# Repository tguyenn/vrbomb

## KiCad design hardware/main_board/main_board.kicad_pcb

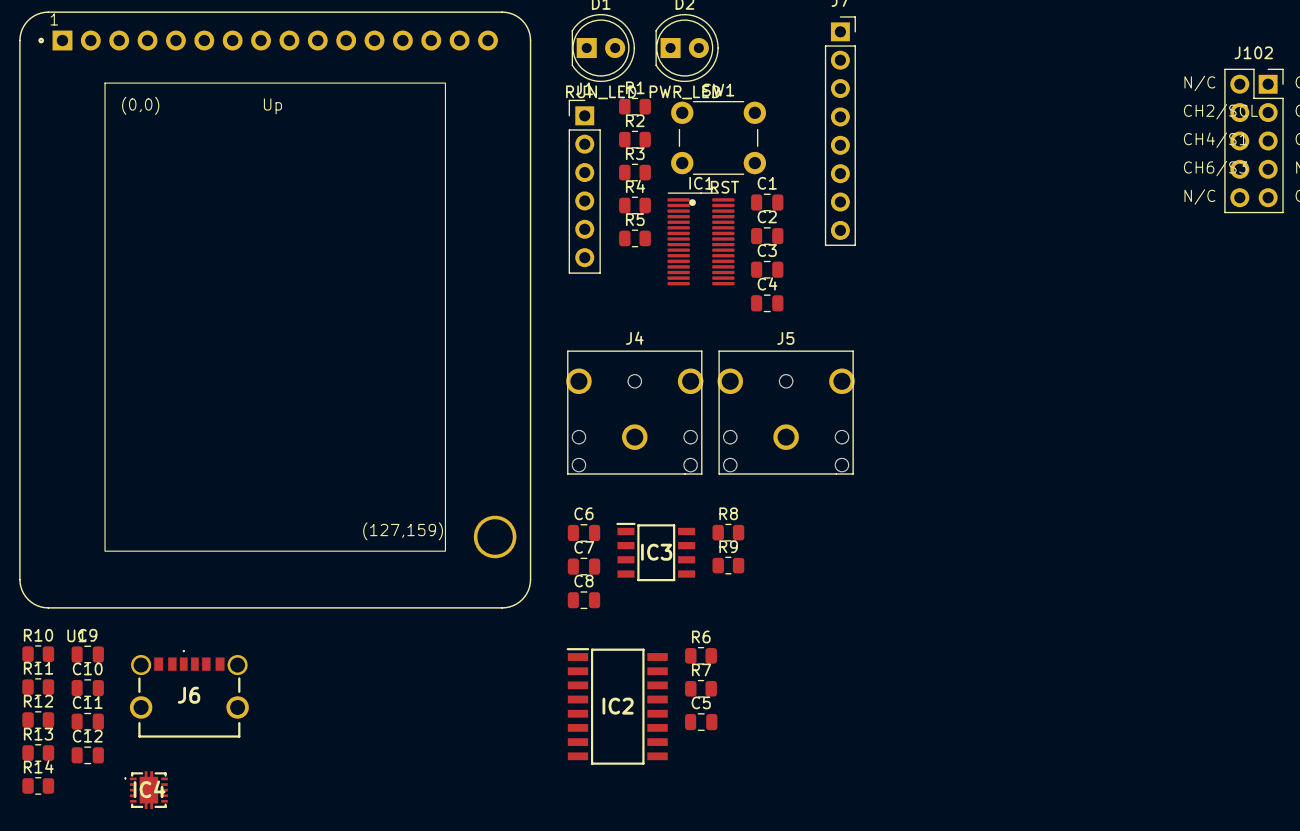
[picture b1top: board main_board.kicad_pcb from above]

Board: 2 copper layers, 40 parts (0 on the bottom side), 41 nets, no tracks yet.

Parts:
C1: 0.47uF; C_0805_2012Metric
C2: 10nF; C_0805_2012Metric
C3: 10uF; C_0805_2012Metric
C4: 0.1uF; C_0805_2012Metric
C5, C6, C8: 1u; C_0805_2012Metric
C7: 0u33; C_0805_2012Metric
C9, C10, C11: 10u; C_0805_2012Metric
C12: u1; C_0805_2012Metric
D1: RUN_LED; LED_D5.0mm
D2: PWR_LED; LED_D5.0mm
IC1: M0G3507QDGS32RQ1; generic_VSSOP_0.5mm
IC2: SN74HC157NSR; SOIC127P780X200-16N
IC3: LM4890M_NOPB; ti_LM4890M_NOPB
IC4: TPS63000IDRCRQ1
J1: Conn_01x06_Pin; PinHeader_1x06_P2.54mm_Vertical
J4, J5: AudioJack; Jack_3.5mm_CUI_SJ1-3523N_Horizontal
J6: UJC-H-G-SMT-1-P6-TR; UJCHGSMT1P6TR
J7: 1x8 Male Pins; PinSocket_1x08_P2.54mm_Vertical
J102: 2x5 Socket Pins; PinSocket_2x05_P2.54mm_Vertical
R1, R2, R6, R7: 10k; R_0805_2012Metric
R3: 47k; R_0805_2012Metric
R4, R5: 470; R_0805_2012Metric
R8, R9: 20k; R_0805_2012Metric
R10: 100; R_0805_2012Metric
R11: 1M; R_0805_2012Metric
R12, R13: 5k1; R_0805_2012Metric
R14: 200k; R_0805_2012Metric
SW1: RST; SW_PUSH_6mm
U1: HiLetGo_ST7735R; hiletgo_st7735r

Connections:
+3V3: C3.1, C4.1, C10.1, C11.1, IC1.7 (VDD), IC4.1 (VOUT), J1.5, R1.2, R2.2, R3.1, R5.1, R6.2, R7.2, R11.1, U1.2 (VCC), U1.6 (RESET), U1.15 (LED+)
+5V: C6.2, C9.1, IC3.6 (VDD), IC4.5 (VIN), J6.A9 (VBUS), J6.B9 (VBUS), J7.1, R10.1
/Audio IO/ADC_IN: IC1.21 (PA14/CLK_OUT/A0_12), J5.R (ring), J5.T (tip)
/Audio IO/DAC_OUT: C7.1, IC1.22 (PA15/A1_0/DACOUT)
/Encoders & Buttons/ENC1.SW: IC2.2 (1A), R6.1
/Encoders & Buttons/ENC2.SW: IC2.3 (1B), R7.1
/Encoders & Buttons/ENC.CLK: IC1.1 (PA26/A0_1), IC2.9 (3Y)
/Encoders & Buttons/ENC.DT: IC1.2 (PA27/RTC_OUT/A0_0), IC2.7 (2Y)
/Encoders & Buttons/ENC.SW: IC1.28 (PA21/A1_7/VREF-), IC2.4 (1Y)
/Encoders & Buttons/ENC_TOGGLE: IC1.32 (PA25/A0_2), IC2.1 (~A/B)
/LCD/CS_LCD: IC1.10 (PA3/LFXIN), U1.10 (TFT_CS)
/LCD/CS_SD: IC1.9 (PA2/ROSC), U1.14 (SDC_CS)
/LCD/LCD_DC: IC1.14 (PA7/CLK_OUT), U1.7 (TFTDC)
/LCD/SPI0.MISO: IC1.11 (PA4/LFCLK_IN/LFXOUT), U1.12 (SDC_MISO)
/LCD/SPI0.MOSI: IC1.12 (PA5/HFXIN/FCC_IN), U1.8 (TFTMOSI), U1.13 (SDC_MOSI)
/LCD/SPI0.SCK: IC1.13 (PA6/HFCLK_IN/HFXOUT), U1.9 (TFTSCK), U1.11 (SDCSCK)
/MCU/BSL_INVOKE: IC1.25 (PA18/A1_3), J1.1
/MCU/I2C0.SCL: IC1.5 (PA1), R1.1
/MCU/I2C0.SDA: IC1.4 (PA0), R2.1
/MCU/NRST: C2.1, IC1.6 (NRST), J1.4, R3.2, SW1.2
/MCU/RUN_LED: IC1.15 (PA8), R4.1
/MCU/S0: IC1.17 (PA10/CLK_OUT), J7.4
/MCU/S1: IC1.18 (PA11), J7.5
/MCU/S2: IC1.19 (PA12/FCC_IN), J7.6
/MCU/S3: IC1.20 (PA13), J7.7
/MCU/SWCLK: IC1.27 (PA20/SWCLK), J1.2
/MCU/SWDIO: IC1.26 (PA19/SWDIO), J1.3
GND: C1.2, C2.2, C3.2, C4.2, C5.2, C6.1, C8.2, C12.2, D1.1 (K), D2.1 (K), IC1.8 (VSS), IC2.8 (GND), IC2.15 (~G), IC3.1 (~SHUTDOWN), IC3.7 (GND), IC4.9 (GND), J1.6, J4.S (sleeve), J5.S (sleeve), J6.A12 (GND), J6.B12 (GND), J7.8, J102.9, R12.2, R13.2, R14.2, SW1.1, U1.1 (GND), U1.16 (LED-)
GNDPWR: C9.2, C10.2, C11.2, IC4.3 (PGND_1), IC4.11 (PGND_2), IC4.12 (PGND_3), IC4.13 (PGND_4), IC4.14 (PGND_5), IC4.15 (PGND_6)
unnamed: C7.2, R8.1
unnamed: D1.2 (A), R4.2
unnamed: D2.2 (A), R5.2
unnamed: C1.1, IC1.3 (VCORE)
unnamed: C5.1, IC2.16 (VCC)
unnamed: C8.1, IC3.2 (BYPASS), IC3.3 (+IN)
unnamed: IC3.4 (-IN), R8.2, R9.1
unnamed: IC3.5 (VO_1), J4.R (ring), J4.T (tip), R9.2
unnamed: C12.1, IC4.6 (EN), IC4.7 (PS/SYNC), IC4.8 (VINA), R10.2
unnamed: IC4.10 (FB), R11.2, R14.1
unnamed: J6.A5 (CC1), R13.1
unnamed: J6.B5 (CC2), R12.1

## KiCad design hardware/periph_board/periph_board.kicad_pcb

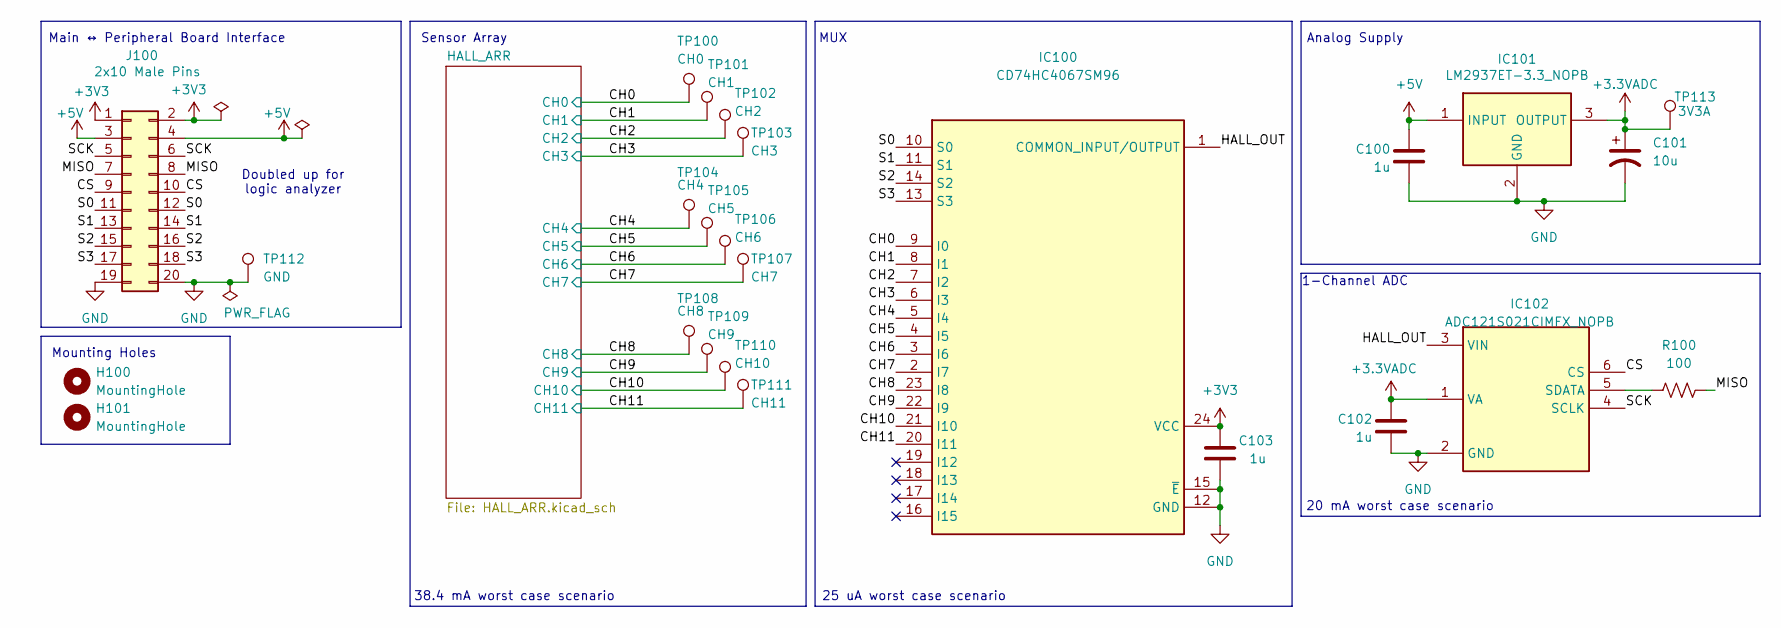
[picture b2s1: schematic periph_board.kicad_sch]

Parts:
C100, C102, C103: 1u; C_0805_2012Metric_Pad1.18x1.45mm_HandSolder
C101: 10u; C_0805_2012Metric
H100, H101: MountingHole; MountingHole_3.2mm_M3
IC100: CD74HC4067SM96; SOP65P780X200-24N; Mouser Part Number 595-CD74HC4067SM96
IC101: LM2937ET-3.3_NOPB; TO254P470X1028X1955-3P; Mouser Part Number 926-LM2937ET-3.3NOPB
IC102: ADC121S021CIMFX_NOPB; SOT95P280X145-6N; Mouser Part Number 926-A121S021CIMFXNPB
J100: 2x10 Male Pins; PinSocket_2x10_P2.54mm_Vertical
R100: 100; R_0805_2012Metric
TP100: CH0; bettertestpoint2
TP101: CH1; bettertestpoint2
TP102: CH2; bettertestpoint2
TP103: CH3; bettertestpoint2
TP104: CH4; bettertestpoint2
TP105: CH5; bettertestpoint2
TP106: CH6; bettertestpoint2
TP107: CH7; bettertestpoint2
TP108: CH8; bettertestpoint2
TP109: CH9; bettertestpoint2
TP110: CH10; bettertestpoint2
TP111: CH11; bettertestpoint2
TP112: GND; bettertestpoint2
TP113: 3V3A; bettertestpoint2

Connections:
+3.3VADC: C101.1, C102.2, IC101.3 (OUTPUT), IC102.1 (VA), TP113.1
+3V3: C103.2, IC100.24 (VCC), J100.1, J100.2; also elsewhere on the board
+5V: C100.2, IC101.1 (INPUT), J100.3, J100.4
/CH0: IC100.9 (I0), TP100.1; also elsewhere on the board
/CH1: IC100.8 (I1), TP101.1; also elsewhere on the board
/CH2: IC100.7 (I2), TP102.1; also elsewhere on the board
/CH3: IC100.6 (I3), TP103.1; also elsewhere on the board
/CH4: IC100.5 (I4), TP104.1; also elsewhere on the board
/CH5: IC100.4 (I5), TP105.1; also elsewhere on the board
/CH6: IC100.3 (I6), TP106.1; also elsewhere on the board
/CH7: IC100.2 (I7), TP107.1; also elsewhere on the board
/CH8: IC100.23 (I8), TP108.1; also elsewhere on the board
/CH9: IC100.22 (I9), TP109.1; also elsewhere on the board
/CH10: IC100.21 (I10), TP110.1; also elsewhere on the board
/CH11: IC100.20 (I11), TP111.1; also elsewhere on the board
/CS: IC102.6 (CS), J100.9, J100.10
/HALL_OUT: IC100.1 (COMMON_INPUT/OUTPUT), IC102.3 (VIN)
/MISO: J100.7, J100.8, R100.2
/S0: IC100.10 (S0), J100.11, J100.12
/S1: IC100.11 (S1), J100.13, J100.14
/S2: IC100.14 (S2), J100.15, J100.16
/S3: IC100.13 (S3), J100.17, J100.18
/SCK: IC102.4 (SCLK), J100.5, J100.6
GND: C100.1, C101.2, C102.1, C103.1, IC100.12 (GND), IC100.15 (~E), IC101.2 (GND), IC102.2 (GND), J100.19, J100.20, TP112.1; also elsewhere on the board
unnamed: IC102.5 (SDATA), R100.1

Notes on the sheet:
Mounting Holes
MUX
Analog Supply
Main ↔ Peripheral Board Interface
38.4 mA worst case scenario
1-Channel ADC
20 mA worst case scenario
Sensor Array
Doubled up for logic analyzer
25 uA worst case scenario

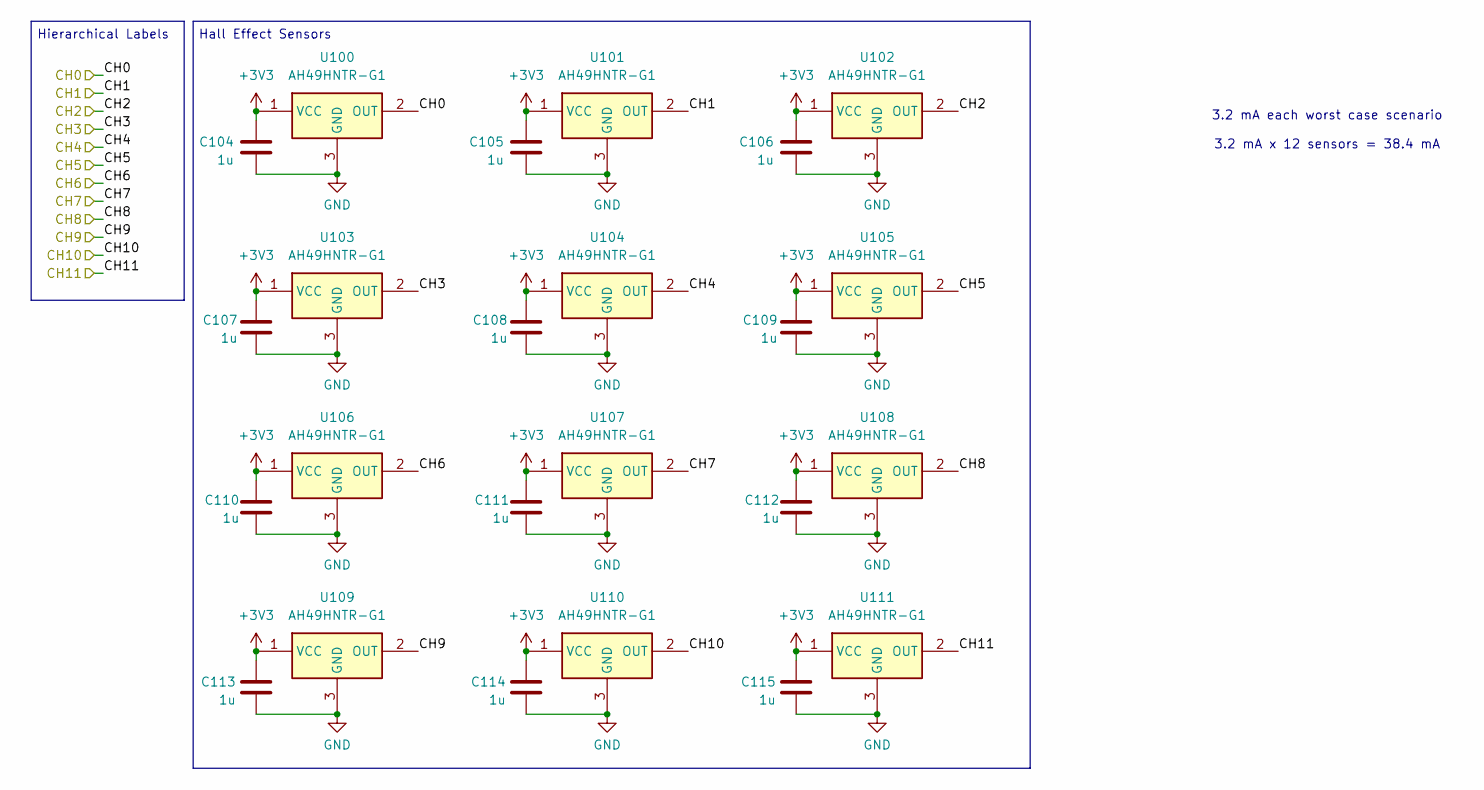
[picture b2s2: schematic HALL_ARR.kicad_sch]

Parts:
C104, C105, C106, C107, C108, C109, C110, C111, C112, C113, C114, C115: 1u; C_0805_2012Metric_Pad1.18x1.45mm_HandSolder
U100, U101, U102, U103, U104, U105, U106, U107, U108, U109, U110, U111: AH49HNTR-G1; SOT95P282X145-3N; Mouser Part Number 621-AH49HNTR-G1

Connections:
+3V3: C104.2, C105.2, C106.2, C107.2, C108.2, C109.2, C110.2, C111.2, C112.2, C113.2, C114.2, C115.2, U100.1 (VCC), U101.1 (VCC), U102.1 (VCC), U103.1 (VCC), U104.1 (VCC), U105.1 (VCC), U106.1 (VCC), U107.1 (VCC), U108.1 (VCC), U109.1 (VCC), U110.1 (VCC), U111.1 (VCC); also elsewhere on the board
/CH0: U100.2 (OUT); also elsewhere on the board
/CH1: U101.2 (OUT); also elsewhere on the board
/CH2: U102.2 (OUT); also elsewhere on the board
/CH3: U103.2 (OUT); also elsewhere on the board
/CH4: U104.2 (OUT); also elsewhere on the board
/CH5: U105.2 (OUT); also elsewhere on the board
/CH6: U106.2 (OUT); also elsewhere on the board
/CH7: U107.2 (OUT); also elsewhere on the board
/CH8: U108.2 (OUT); also elsewhere on the board
/CH9: U109.2 (OUT); also elsewhere on the board
/CH10: U110.2 (OUT); also elsewhere on the board
/CH11: U111.2 (OUT); also elsewhere on the board
GND: C104.1, C105.1, C106.1, C107.1, C108.1, C109.1, C110.1, C111.1, C112.1, C113.1, C114.1, C115.1, U100.3 (GND), U101.3 (GND), U102.3 (GND), U103.3 (GND), U104.3 (GND), U105.3 (GND), U106.3 (GND), U107.3 (GND), U108.3 (GND), U109.3 (GND), U110.3 (GND), U111.3 (GND); also elsewhere on the board

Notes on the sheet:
3.2 mA each worst case scenario 3.2 mA x 12 sensors = 38.4 mA
Hall Effect Sensors
Hierarchical Labels

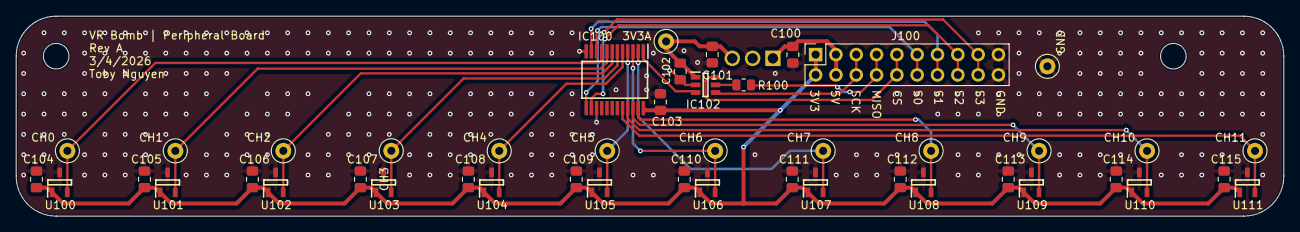
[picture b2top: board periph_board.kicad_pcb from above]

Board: 2 copper layers, 158.5 x 25.0 mm, 49 parts (1 on the bottom side), 25 nets.

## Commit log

2026-03-03 cleaned up unnecessary files
2026-03-03 add deadline
2026-03-05 scorched earth
2026-03-07 Adjusted spacing to 13.5mm between hall effects
2026-03-08 fixed sides of peripheral board not being symmetrical. added teardrops. name of board tbd
2026-03-09 drew schematic
2026-03-10 save before nuke SPI ADC
2026-03-11 port to i2c for both boards. periph board passes drc
2026-03-23 project builds
2026-03-28 analog mux select line scanning
2026-03-29 finished main pcb
2026-03-31 prod files
